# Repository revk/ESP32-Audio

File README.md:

## Amazon

This part if for Amazon - as this is the *manufacturers web site* and so used as proof of title and list price. It is also links to where you can buy.

|ASIN|List price|Title|
|-----|----|----|
|[B0DQH9SK8K](https://www.amazon.co.uk/dp/B0DQH9SK8K)|£35.00|Small ESP32-S3 high quality voice recorder board with stereo TDK ICS 43434 microphones, micro SD card slot, and charger circuit|

## Trademark

This is an open source project, but bear in mind you cannot sell boards bearing the Andrews & Arnold Ltd name, the A&A logo, the registered trademark AJK logo, or the GS1 allocated EANs assigned to Andrews & Arnold Ltd.

# Open†Mic

(† Open source)

This project provides software and PCB designs for working with I2S microphone and speaker, most notably a self contained battery operated audio recorder to micro SD card.

The software provides working for a number of different use cases.

The hardware is an audio recorder, but the [LED](https://github.com/revk/ESP32-LED) project also has audio hardware with microphones and speakers.

## Why use this?

There are loads of microphones and dictaphones at sensible prices, so why use this?

The main reason is flexibility - it is open source - the hardware can do a lot, and it already allows record to SD and upload by web post. It can eventually be a Bluetooth microphone, or a telephone or intercom, etc. You get to do what you like, and can make suggestions and pull requests and load your own code.

The other feature, which is becoming rarer these days, is that it is *stand alone*. No subscription. No accounts or sign up. No cloud services. Nobody training AI on your data.

## Button

Button works with short or long press (long is 3s).

* press to answer or end incoming SIP call
* press to start or stop recording
* hold (1s) to reject incoming SIP call
* hold (1s) to make a call
* hold (3s) to enter power off (will upload files at this point if option selected) - there is also an auto power off feature
* press to power back on

## Microphone

The software is designed to work with I2S audio input, and is coded and tested for two specific microphones. Others may work, but I2S has a number of options - so ask me if you need some other settings.

* [TDK T3902](https://www.lcsc.com/datasheet/lcsc_datasheet_2401291125_TDK-InvenSense-MMICT390200012_C3171752.pdf) is an I2S PDM microphone (so 16 bits per sample)
* [TDK ICS-43434](https://www.lcsc.com/datasheet/lcsc_datasheet_2312010321_TDK-InvenSense-ICS-43434_C5656610.pdf) is an I2S microphone (24 bits) with sample rates up to 51.6kHz

The software can work with one or two microphones (i.e. mono or stereo). When two microphones, they are the same type, on the same bus, with one wired as *left* and one as *right* channel. 

## Speaker

For I2S output the [MAX98357A](https://www.lcsc.com/datasheet/lcsc_datasheet_2106070436_Analog-Devices-Inc--Maxim-Integrated-MAX98357AEWL-T_C2682619.pdf) is recommended. This can be one chip working as *left*, *right*, or *left+right* channels, or as two chips on the same bus, one as *left* and one as *right*.

* `spkrate` sets the speaker rate, which (for the MAX98357A) can be 8kHz, 16kHz, 32kHz, 44.1kHz, 48kHz, 88.2kHz, or 96kHz.

## Input processing

The input from the I2S microphones can be mono or stereo, and can be 16 or 24 bits. If a PDM microphone is used it is always 16 bits. If the ICS-43434 microphone is used it is received as 24 bits which can either be passed on unprocessed, or converted to 16 bits.

* `micws` is the GPIO for the channel, if not set it is assumed to be PDM mode
* `micrate` sets the sample rate
* `micstereo` is set for stereo working
* `micright` is set for *right* channel when mono.
* `micgain` sets the gain for processing 24 bits to 16

When `micgain` is set to `0`, or when using a PDM microphone, the samples (stereo or mono) are used as received, with no processing. This means for PDM mode this is 16 bits per sample, and for ICS-43434 it is 24 bits per sample.

When `micgain` is not `0`, for ICS-43434, the 24 bit samples are processed by multiplying by `micgain/256` and clipping to 16 bits (`-32768` to `32767`). A `micgain` of `8` works well for speech.

## Output

The output via the speaker can be one of the following - normally managed via MQTT control messages or web interface, though SIP is automatic when a call arrives.

* Morse code (including prosigns in `[]`, e.g. `[INT]`) and punctuation
* DTMF
* Playing a WAV file from SD card (TODO)
* SIP (see below)

The format will depend on the source - the MAX98357A can handle 16, 24, or 32 bits per channel.

## Audio recorder

The main use of this software is as an *audio recorder*. This will record from the microphone(s) to a WAV file on the micro SD card. It allows a `button` GPIO to start/stop recording and power on/off. It allows for a separate WS2812 record status LED. The PCB design includes LiPo charging.

Options are planned:-

* Stream audio over WiFI by some means
* Stream audio over bluetooth, if ever I work out how to do that

An option exists to upload files to a web page as a `POST`, renaming the file slightly once uploaded so not uploaded twice. This is done when you hold the button to *power off`*.

An option exists to delete old files if space needed for new file.

## SIP working

The software allows settings `siphost`, `sipuser`, and `sippass`, such that the device registers with a SIP server.

Once registered it can then accept a call, and pass audio both ways over RTP, 8kHz alaw. Only one call at a time.

* The microphone is changed to mono (channel selected by `micright`) 8kHz, and either 16 bit PDM, or processed 24 bit to 16 bit using `micgain`, and then companded to alaw.
* The speaker is sent dual mono audio expanded from 8kHz alaw to 16 bits per sample.

Note that there is no echo cancellation, so a caller is likely to hear their own audio come back to them.

Once the call is complete, the audio processing reverts to previous settings.

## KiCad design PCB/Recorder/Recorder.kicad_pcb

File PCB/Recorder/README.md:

# Audio recorder board

The Audio record board provides a shirt mount Audio board.

Features

* LiPo battery handling and charging
* Mic, stereo TDK ICS 43434 24 bit
* SD card slot
* Button to start/stop recording, etc.

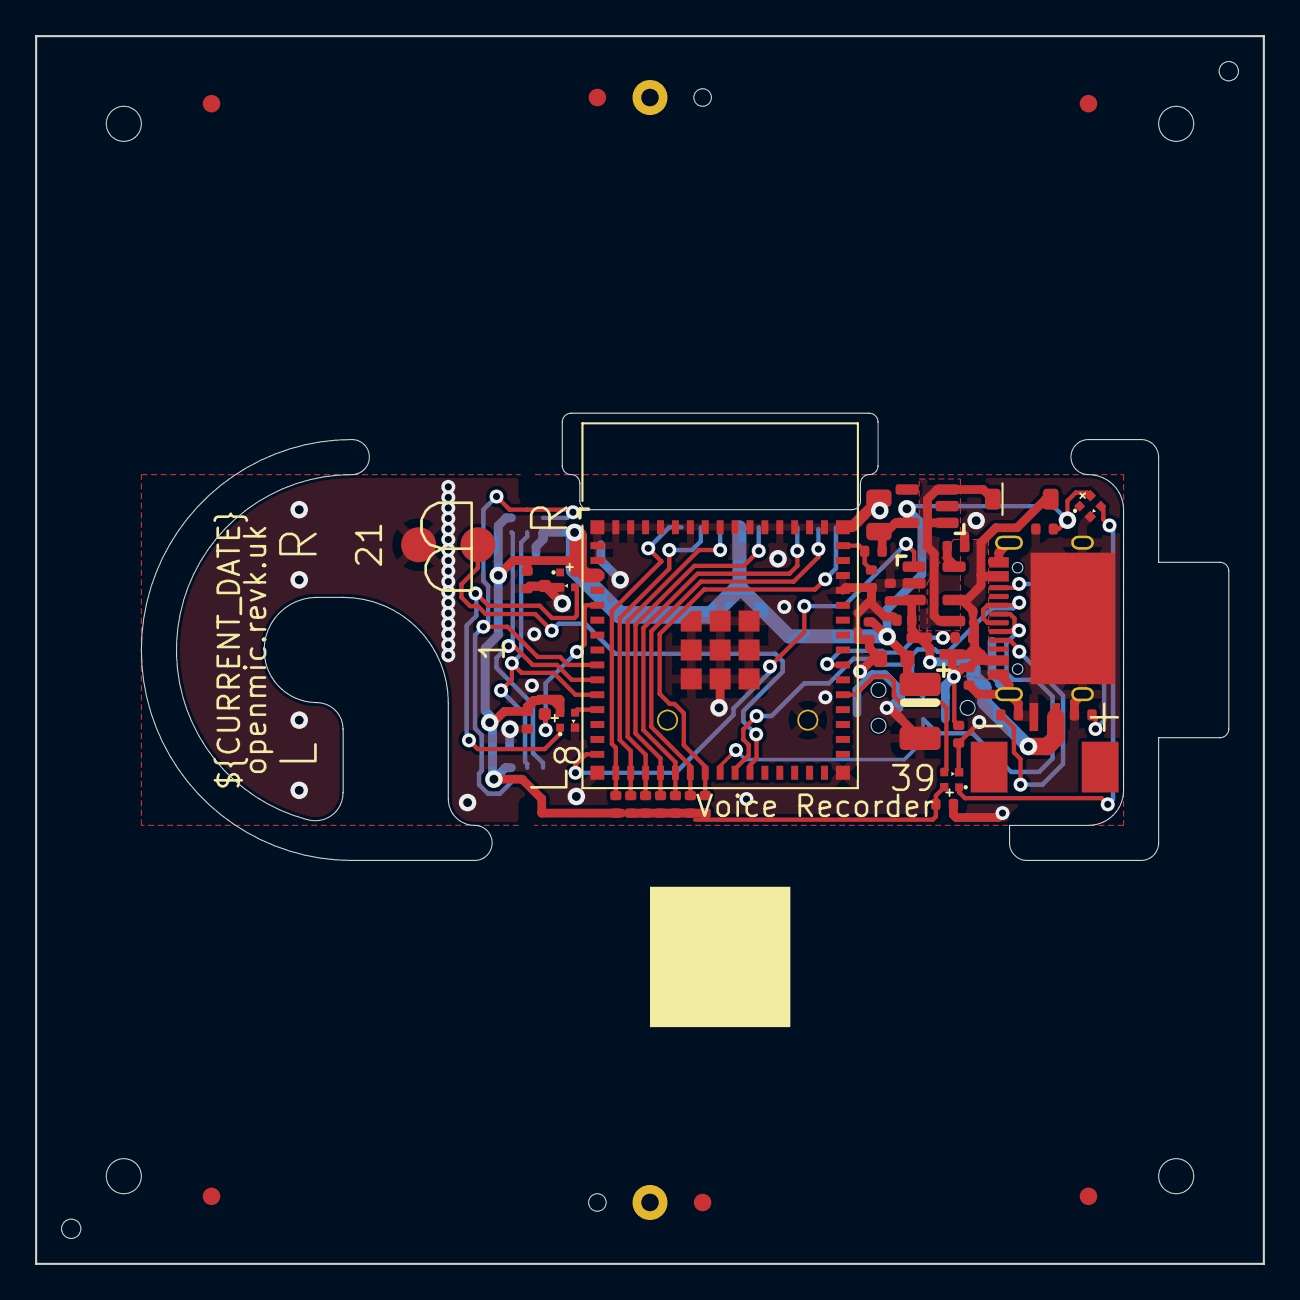
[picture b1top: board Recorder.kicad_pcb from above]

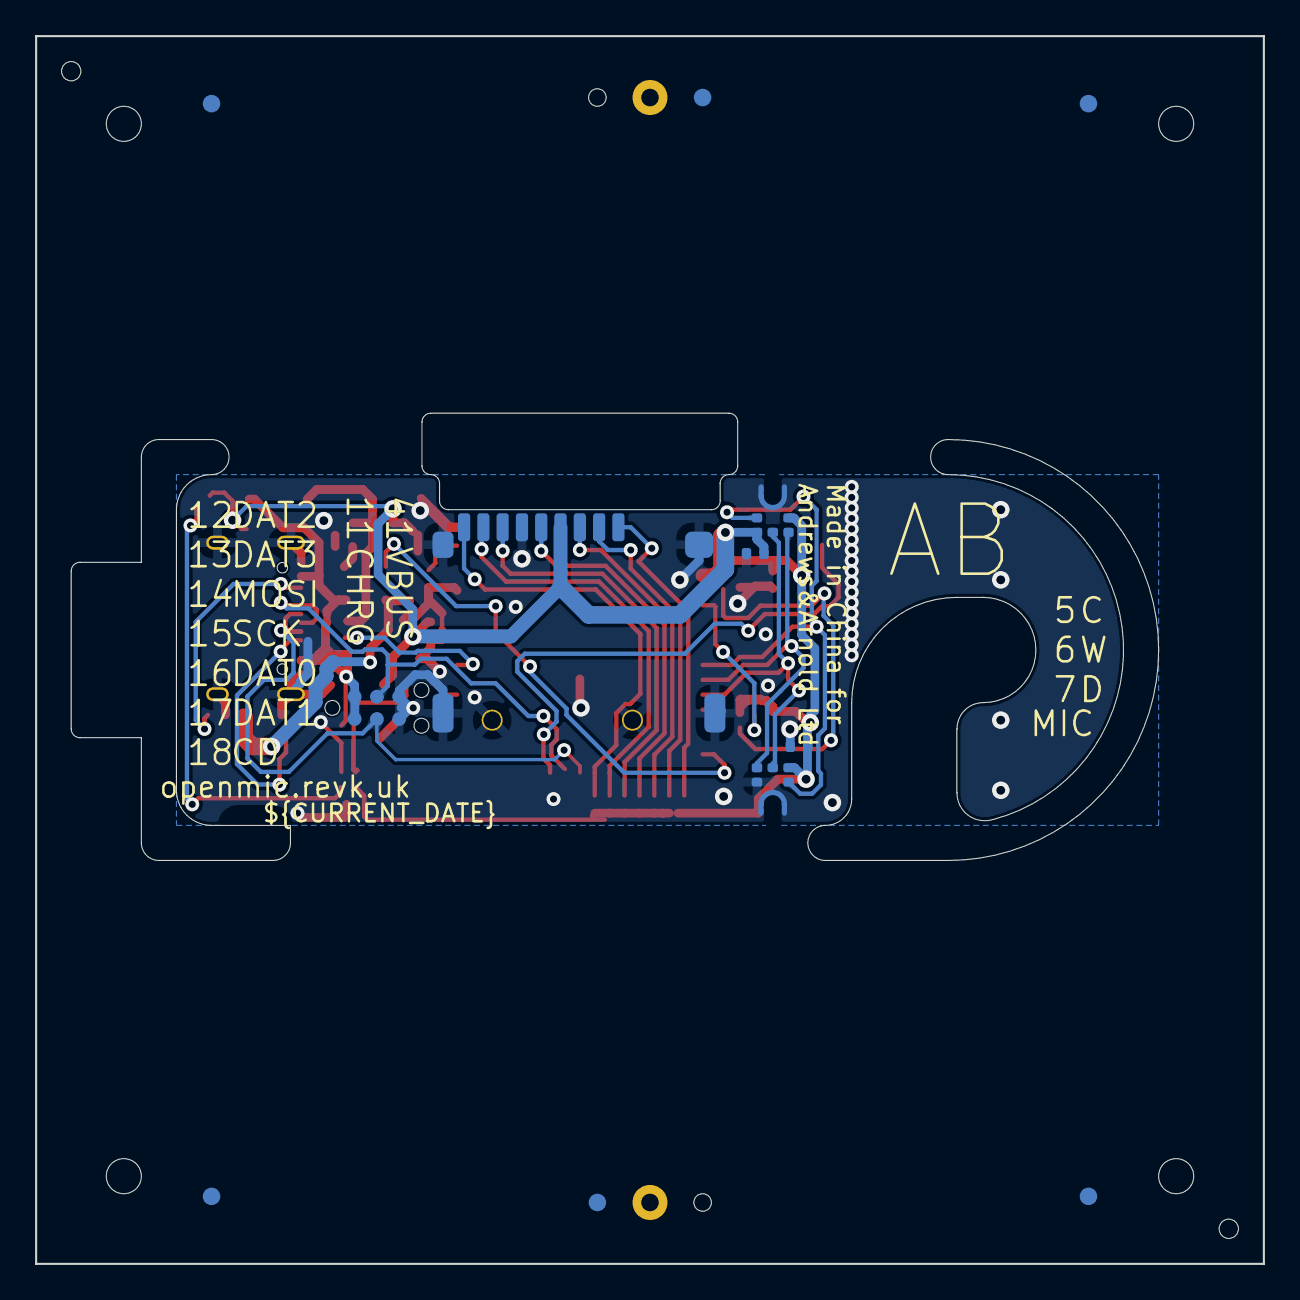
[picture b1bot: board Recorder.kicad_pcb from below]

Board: 2 copper layers, 70.0 x 70.0 mm, 47 parts (7 on the bottom side), 29 nets.

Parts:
C1: 220uF Tant; CP_EIA-3528-21_Kemet-B
C2, C4, C5, C6, C8, C10, C13: 100nF; C_0402
C3: 22uF; C_0603
C7, C11: 10uF 6.3V; C_0402
C9: 1uF; C_0402
C16: 100uF; C_0805
D1, D4, D5, D6: XL-1010RGBC-WS2812B; SMD1010
D2: DFN1006-2L
D3: MBR0530; D_SOD-123
J1: Battery; 1.25T-2PWT (Molex 532610271)
J2: Reset; AA-Pad
J3: TC2030-USB-NL-DS; Tag-Connect_TC2030-IDC-NL_2x03_P1.27mm_Vertical
J4: TF_PUSH
J5: USB-C-Socket-H
PCB1: 70x70; PCB7070
Q2: CJ2301; SOT-23
R1, R2, R3, R7, R8, R9, R10, R11, R12, R13, R14: 10K; R_0402
R5, R6: 5K1; R_0402
SW1: SW_Push; TS-1092S-B3D2-G
U1: R; ICS43434_MEMS_Mic_Open
U2: L; ICS43434_MEMS_Mic_Open
U3: TP4054; SOT-23-5
U4: ME6211C33M5G-N; SOT-23-5
U6: ESP32-S3-MINI-1
V1, V2: VCUT70N

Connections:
+3V3: C1.1, C2.1, C3.1, C4.1, C5.1, C6.1, C8.2, C10.1, C13.2, C16.1, D1.2 (+), D4.2 (+), D5.2 (+), D6.2 (+), J4.4 (VDD), R2.1, R3.1, R9.1, R10.1, R11.1, R12.1, R13.1, R14.1, U1.2 (LR), U1.5 (VDD), U2.5 (VDD), U4.5 (OUT), U6.3 (3V3)
BLINK: D1.4 (I), U6.35 (GPIO39)
BUTTON: SW1.2, U6.5 (GPIO1)
CHARGING: U3.1 (STAT), U6.15 (GPIO11)
D+: J3.4 (D+), J5.A6 (D+), J5.B6 (D+), U6.24 (GPIO20)
D-: J3.3 (D-), J5.A7 (D-), J5.B7 (D-), U6.23 (GPIO19)
GND: C1.2, C2.2, C3.2, C4.2, C5.2, C6.2, C7.2, C8.1, C9.2, C10.2, C11.2, C13.1, C16.2, D1.3 (-), D2.1, D4.3 (-), D5.3 (-), D6.3 (-), J1.2, J2.1, J3.5 (GND), J3.6 (GND), J4.6 (VSS), J4.S (SHIELD), J5.A1 (GND), J5.A12 (GND), J5.B1 (GND), J5.B12 (GND), J5.S1 (SHIELD), R1.1, R5.2, R6.1, R8.2, SW1.1, U1.3 (GND), U2.2 (LR), U2.3 (GND), U3.2 (VSS), U4.2 (GND), U6.1 (GND), U6.2 (GND), U6.42 (GND), U6.43 (GND), U6.46 (GND), U6.47 (GND), U6.48 (GND), U6.49 (GND), U6.50 (GND), U6.51 (GND), U6.52 (GND), U6.53 (GND), U6.54 (GND), U6.55 (GND), U6.56 (GND), U6.57 (GND), U6.58 (GND), U6.59 (GND), U6.60 (GND), U6.61 (GND), U6.62 (GND), U6.63 (GND), U6.64 (GND), U6.65 (GND)
LEDMIC: D5.4 (I), U6.12 (GPIO8)
unnamed: D1.1 (O), D6.4 (I)
unnamed: D3.1 (K), Q2.2 (S), U4.1 (IN), U4.3 (EN)
unnamed: D4.4 (I), D5.1 (O)
unnamed: J2.2, U6.25 (GPIO21)
unnamed: J5.A5 (CC1), R5.1
unnamed: J5.B5 (CC2), R6.2
unnamed: R1.2, U3.5 (PROG)
unnamed: C9.1, R2.2, U6.45 (EN)
unnamed: R7.1, U6.37 (GPIO41)
SCK: U1.4 (SCK), U2.4 (SCK), U6.9 (GPIO5)
SD: U1.6 (SD), U2.6 (SD), U6.11 (GPIO7)
SDCD: J4.9 (CD), R3.2, U6.22 (GPIO18)
SDCLK: J4.5 (CLK), R11.2, U6.19 (GPIO15)
SDCMD: J4.3 (CMD), R12.2, U6.18 (GPIO14)
SDDAT0: J4.7 (DAT0), R10.2, U6.20 (GPIO16)
SDDAT1: J4.8 (DAT1), R9.2, U6.21 (GPIO17)
SDDAT2: J4.1 (DAT2), R14.2, U6.16 (GPIO12)
SDDAT3: J4.2 (DAT3/CD), R13.2, U6.17 (GPIO13)
VBAT: C7.1, D2.2, J1.1, Q2.3 (D), U3.3 (VBAT)
VBUS: C11.1, D3.2 (A), J3.1 (VBUS), J3.2 (VBUS), J5.A4 (VBUS), J5.A9 (VBUS), J5.B4 (VBUS), J5.B9 (VBUS), Q2.1 (G), R7.2, R8.1, U3.4 (VDD)
WS: U1.1 (WS), U2.1 (WS), U6.10 (GPIO6)

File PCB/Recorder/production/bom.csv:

Designator,Footprint,Quantity,Value,LCSC Part #
C1,CP_EIA-3528-21_Kemet-B,1,220uF Tant,C122649
"C10, C13, C2, C4, C5, C6, C8",C_0402,7,100nF,
"C11, C7",C_0402,2,10uF 6.3V,C15525
C16,C_0805,1,100uF,C141660
C3,C_0603,1,22uF,
C9,C_0402,1,1uF,
"D1, D4, D5, D6",SMD1010,4,XL-1010RGBC-WS2812B,C5349953
D2,DFN1006-2L,1,~,C5137770
D3,D_SOD-123,1,MBR0530,
J1,1.25T-2PWT (Molex 532610271),1,Battery,C177225
J4,TF_PUSH,1,TF_PUSH,C393941
J5,USB-C-Socket-H,1,USB-C-Socket-H,C709357
Q2,SOT-23,1,CJ2301,C8547
"R1, R10, R11, R12, R13, R14, R2, R3, R7, R8, R9",R_0402,11,10K,
"R5, R6",R_0402,2,5K1,
SW1,TS-1092S-B3D2-G,1,SW_Push,
U1,ICS43434_MEMS_Mic_Open,1,R,C5656610
U2,ICS43434_MEMS_Mic_Open,1,L,C5656610
U3,SOT-23-5,1,TP4054,C668215
U4,SOT-23-5,1,ME6211C33M5G-N,C82942
U6,ESP32-S3-MINI-1,1,ESP32-S3-MINI-1,C3013941

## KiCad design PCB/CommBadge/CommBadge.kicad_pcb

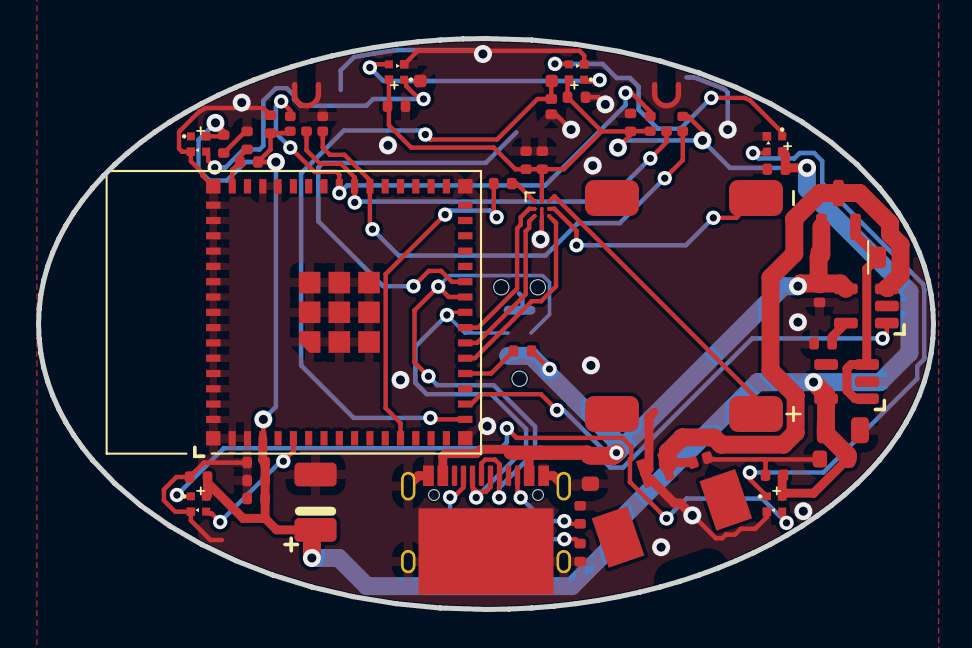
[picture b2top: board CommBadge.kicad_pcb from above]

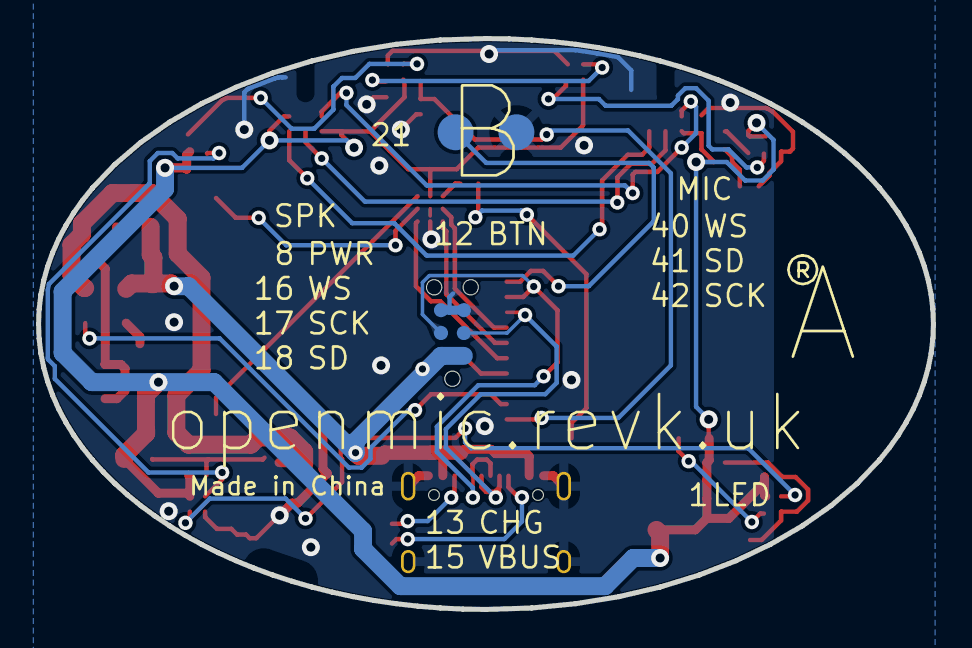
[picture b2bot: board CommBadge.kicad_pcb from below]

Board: 2 copper layers, 49.7 x 31.7 mm, 47 parts (2 on the bottom side), 31 nets.

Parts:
C1: 220uF Tant; CP_EIA-3528-21_Kemet-B
C2, C6, C10, C11, C12, C14, C15, C16, C17, C18: 100nF; C_0402
C3: 22uF; C_0603
C4: 100uF; C_0805
C5: 10uF 35V; C_0603
C7, C8, C13: 10uF; C_0402
C9: 1uF; C_0402
D1, D3: DFN1006-2L
D2: MBR0530; D_SOD-123
D4, D5, D6, D7, D8, D9: XL-1010RGBC-WS2812B; SMD1010
J1: Reset; AA-Pad
J2: Battery; 1.25T-2PWT (Molex 532610271)
J3: TC2030-USB-NL-DS; Tag-Connect_TC2030-IDC-NL_2x03_P1.27mm_Vertical
J5: USB-C-Socket-H
LS1: Speaker; KLJ-Speaker
Q1: CJ2301; SOT-23
R1, R2, R3, R4: 10K; R_0402
R5, R6: 5K1; R_0402
R8: 634K; R_0402
SW2: SW_Push; TS-1092S-B3D2-G
U2: MAX98357A; WLP-1.437mmx1.347mm-0.21mm-ball
U3: TP4054; SOT-23-5
U4: ME6211C33M5G-N; SOT-23-5
U5: L; ICS43434_MEMS_Mic_Open
U6: ESP32-S3-MINI-1
U7: R; ICS43434_MEMS_Mic_Open

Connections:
+3V3: C1.1, C2.1, C3.1, C4.1, C6.2, C7.1, C8.1, C10.2, C11.1, C12.1, C13.1, C14.1, C15.1, C16.1, C17.1, C18.1, D4.2 (+), D5.2 (+), D6.2 (+), D7.2 (+), D8.2 (+), D9.2 (+), R2.1, U2.A2 (VDD), U4.5 (OUT), U5.5 (VDD), U6.3 (3V3), U7.2 (LR), U7.5 (VDD)
CHARGING: U3.1 (STAT), U6.17 (GPIO13)
D+: J3.4 (D+), J5.A6 (D+), J5.B6 (D+), U6.24 (GPIO20)
D-: J3.3 (D-), J5.A7 (D-), J5.B7 (D-), U6.23 (GPIO19)
GND: C1.2, C2.2, C3.2, C4.2, C5.2, C6.1, C7.2, C8.2, C9.2, C10.1, C11.2, C12.2, C13.2, C14.2, C15.2, C16.2, C17.2, C18.2, D1.1, D3.1, D4.3 (-), D5.3 (-), D6.3 (-), D7.3 (-), D8.3 (-), D9.3 (-), J1.1, J2.2, J3.5 (GND), J3.6 (GND), J5.A1 (GND), J5.A12 (GND), J5.B1 (GND), J5.B12 (GND), J5.S1 (SHIELD), R1.1, R3.2, R5.2, R6.1, SW2.1, U2.B2 (GAIN_SLOT), U2.C2 (GND), U3.2 (VSS), U4.2 (GND), U5.2 (LR), U5.3 (GND), U6.1 (GND), U6.2 (GND), U6.42 (GND), U6.43 (GND), U6.46 (GND), U6.47 (GND), U6.48 (GND), U6.49 (GND), U6.50 (GND), U6.51 (GND), U6.52 (GND), U6.53 (GND), U6.54 (GND), U6.55 (GND), U6.56 (GND), U6.57 (GND), U6.58 (GND), U6.59 (GND), U6.60 (GND), U6.61 (GND), U6.62 (GND), U6.63 (GND), U6.64 (GND), U6.65 (GND), U7.3 (GND)
MICSCK: U5.4 (SCK), U6.38 (GPIO42), U7.4 (SCK)
MICSD: U5.6 (SD), U6.37 (GPIO41), U7.6 (SD)
MICWS: U5.1 (WS), U6.36 (GPIO40), U7.1 (WS)
unnamed: D2.1 (K), Q1.2 (S), U4.1 (IN), U4.3 (EN)
unnamed: D4.4 (I), D9.1 (O)
unnamed: D4.1 (O), D5.4 (I)
unnamed: D5.1 (O), D8.4 (I)
unnamed: D6.4 (I), D8.1 (O)
unnamed: D6.1 (O), D7.4 (I)
unnamed: J1.2, U6.25 (GPIO21)
unnamed: J5.A5 (CC1), R5.1
unnamed: J5.B5 (CC2), R6.2
unnamed: LS1.2, U2.B3 (OUTN)
unnamed: LS1.1, U2.A3 (OUTP)
unnamed: R8.1, U2.A1 (~SD_MODE)
unnamed: R1.2, U3.5 (PROG)
unnamed: C9.1, R2.2, U6.45 (EN)
unnamed: R4.2, U6.19 (GPIO15)
PUSH: D3.2, SW2.2, U6.16 (GPIO12)
RGB: D9.4 (I), U6.5 (GPIO1)
SKPPWR: R8.2, U6.12 (GPIO8)
SKPSCK: U2.C1 (BCLK), U6.21 (GPIO17)
SKPSD: U2.B1 (DIN), U6.22 (GPIO18)
SKPWS: U2.C3 (LRCLK), U6.20 (GPIO16)
VBAT: D1.2, J2.1, Q1.3 (D), U3.3 (VBAT)
VBUS: C5.1, D2.2 (A), J3.1 (VBUS), J3.2 (VBUS), J5.A4 (VBUS), J5.A9 (VBUS), J5.B4 (VBUS), J5.B9 (VBUS), Q1.1 (G), R3.1, R4.1, U3.4 (VDD)

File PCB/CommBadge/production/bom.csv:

Designator,Footprint,Quantity,Value,LCSC Part #
C1,CP_EIA-3528-21_Kemet-B,1,220uF Tant,C122649
"C10, C11, C12, C14, C15, C16, C17, C18, C2, C6",C_0402,10,100nF,
"C13, C7, C8",C_0402,3,10uF,C15525
C3,C_0603,1,22uF,
C4,C_0805,1,100uF,C141660
C5,C_0603,1,10uF 35V,C194427
C9,C_0402,1,1uF,
"D1, D3",DFN1006-2L,2,~,C5137770
D2,D_SOD-123,1,MBR0530,
"D4, D5, D6, D7, D8, D9",SMD1010,6,XL-1010RGBC-WS2812B,C5349953
J2,1.25T-2PWT (Molex 532610271),1,Battery,C177225
J5,USB-C-Socket-H,1,USB-C-Socket-H,C709357
LS1,KLJ-Speaker,1,Speaker,C18186315
Q1,SOT-23,1,CJ2301,C5224170
"R1, R2, R3, R4",R_0402,4,10K,
"R5, R6",R_0402,2,5K1,
R8,R_0402,1,634K,
SW2,TS-1092S-B3D2-G,1,SW_Push,
U2,WLP-1.437mmx1.347mm-0.21mm-ball,1,MAX98357A,
U3,SOT-23-5,1,TP4054,C668215
U4,SOT-23-5,1,ME6211C33M5G-N,C82942
U5,ICS43434_MEMS_Mic_Open,1,L,C5656610
U6,ESP32-S3-MINI-1,1,ESP32-S3-MINI-1,C3013941
U7,ICS43434_MEMS_Mic_Open,1,R,C5656610

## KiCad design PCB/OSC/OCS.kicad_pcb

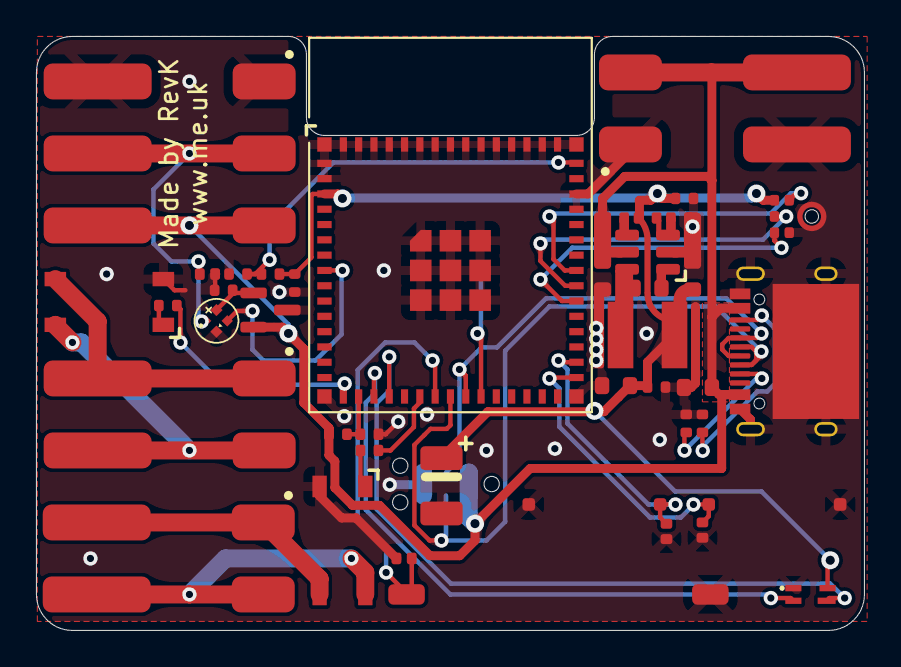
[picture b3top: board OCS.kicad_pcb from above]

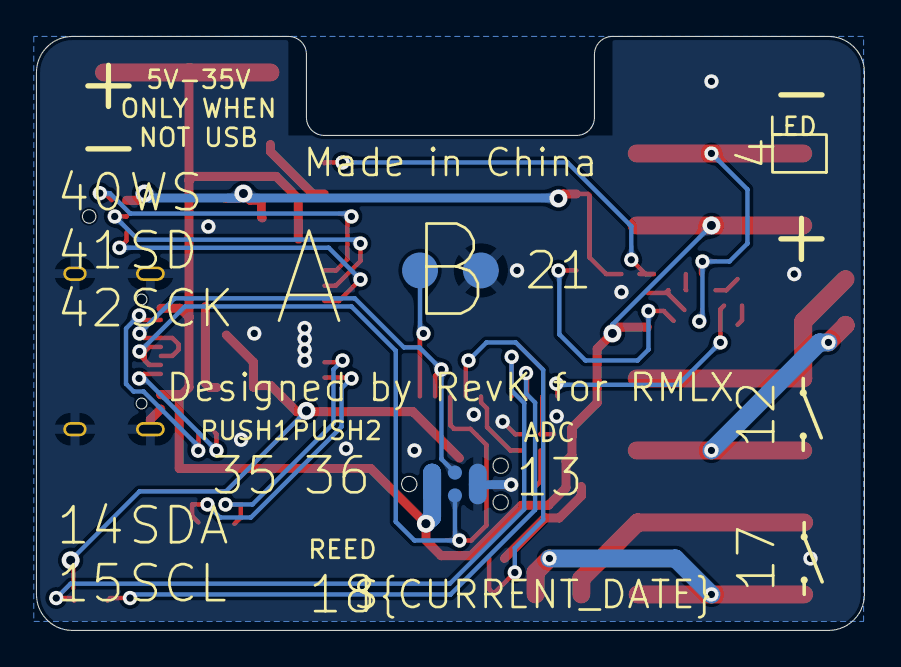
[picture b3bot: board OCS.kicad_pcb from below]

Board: 2 copper layers, 46.0 x 33.0 mm, 44 parts (2 on the bottom side), 29 nets.

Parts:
C1: 220uF Tant; CP_EIA-3528-21_Kemet-B
C2, C15: 100nF; C_0402
C3: 22uF; C_0603
C5: 10uF 35V; C_0603
C7, C8: 10uF; C_0402
C9: 1uF; C_0402
C10: 10uF 35V; C_0603_
C11: 10uF 6.3V; C_0603_
C12: 100nF; C_0603_
D1: XL-1010RGBC-WS2812B; SMD1010
D2, D3, D4, D5: DFN1006-2L
J1: Reset; AA-Pad
J2: Wago; WAGO-2060-453-998-404
J3: TC2030-USB-NL-DS; Tag-Connect_TC2030-IDC-NL_2x03_P1.27mm_Vertical
J4: DC; WAGO-2060-452-998-404
J5: USB-C-Socket-H
J6: RELAY1; WAGO-2060-452-998-404
J7: RELAY2; WAGO-2060-452-998-404
L2: 10uH; L_4x4_
R1: 124K; R_0402
R2, R3: 10K; R_0402
R4: 124k; R_0402_
R5, R6: 5K1; R_0402
R7, R10: 1K; R_0402
R14: 39k2; R_0402_
R15: 1M; R_0402_
SW1, SW3: SW_Push; TS-1092S-B3D2-G
SW2: SW_Reed; Reed-59170
U1: ICS43434_MEMS_Mic
U3, U8: Relay; SO-4_4.4x4.3mm_P2.54mm
U4: 78L05; SOT-23
U6: ESP32-S3-MINI-1
U7: MD8942; SOT-23-6-MD8942
U9: VEML6040

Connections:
+3V3: C1.1, C2.1, C3.1, C7.1, C8.1, R2.1, U1.5 (VDD), U6.3 (3V3), U7.8 (VOUT), U9.4 (VDD)
ADC: R1.2, R3.1, U6.17 (GPIO13)
D+: J3.4 (D+), J5.A6 (D+), J5.B6 (D+), U6.24 (GPIO20)
D-: J3.3 (D-), J5.A7 (D-), J5.B7 (D-), U6.23 (GPIO19)
DC: C5.1, J2.3, J3.1 (VBUS), J3.2 (VBUS), J4.2, J5.A4 (VBUS), J5.A9 (VBUS), J5.B4 (VBUS), J5.B9 (VBUS), R1.1, U4.2 (IN), U7.5 (VIN)
GND: C1.2, C2.2, C3.2, C5.2, C7.2, C8.2, C9.2, C15.2, D1.3 (-), D2.1, D3.1, D4.1, D5.1, J1.1, J2.1, J3.5 (GND), J3.6 (GND), J4.1, J5.A1 (GND), J5.A12 (GND), J5.B1 (GND), J5.B12 (GND), J5.S1 (SHIELD), R3.2, R5.2, R6.1, SW1.1, SW2.2, SW3.1, U1.2 (LR), U1.3 (GND), U3.2, U4.3 (GND), U6.1 (GND), U6.2 (GND), U6.42 (GND), U6.43 (GND), U6.46 (GND), U6.47 (GND), U6.48 (GND), U6.49 (GND), U6.50 (GND), U6.51 (GND), U6.52 (GND), U6.53 (GND), U6.54 (GND), U6.55 (GND), U6.56 (GND), U6.57 (GND), U6.58 (GND), U6.59 (GND), U6.60 (GND), U6.61 (GND), U6.62 (GND), U6.63 (GND), U6.64 (GND), U6.65 (GND), U7.2 (GND), U7.7 (GND), U8.2, U9.1 (GND)
LED1: D1.4 (I), U6.8 (GPIO4)
LED2: D1.1 (O), D2.2, J2.2
MICSCK: U1.4 (SCK), U6.38 (GPIO42)
MICSD: U1.6 (SD), U6.37 (GPIO41)
MICWS: U1.1 (WS), U6.36 (GPIO40)
unnamed: C15.1, D1.2 (+), U4.1 (OUT)
unnamed: J1.2, U6.25 (GPIO21)
unnamed: J5.A5 (CC1), R5.1
unnamed: J5.B5 (CC2), R6.2
unnamed: J6.1, U3.3
unnamed: J6.2, U3.4
unnamed: J7.1, U8.3
unnamed: J7.2, U8.4
unnamed: R7.1, U3.1
unnamed: R10.1, U8.1
unnamed: C9.1, R2.2, U6.45 (EN)
PUSH1: D3.2, SW3.2, U6.31 (GPIO35)
PUSH2: D4.2, SW1.2, U6.32 (GPIO36)
REED: D5.2, SW2.1, U6.22 (GPIO18)
RELAY1: R7.2, U6.16 (GPIO12)
RELAY2: R10.2, U6.21 (GPIO17)
SCL: U6.19 (GPIO15), U9.3 (SCL)
SDA: U6.18 (GPIO14), U9.2 (SDA)

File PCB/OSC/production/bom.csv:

Designator,Footprint,Quantity,Value,LCSC Part #
C1,CP_EIA-3528-21_Kemet-B,1,220uF Tant,C122649
C10,C_0603_,1,10uF 35V,C194427
C11,C_0603_,1,10uF 6.3V,C1691
C12,C_0603_,1,100nF,
"C15, C2",C_0402,2,100nF,
C3,C_0603,1,22uF,
C5,C_0603,1,10uF 35V,C194427
"C7, C8",C_0402,2,10uF,C15525
C9,C_0402,1,1uF,
D1,SMD1010,1,XL-1010RGBC-WS2812B,C5349953
"D2, D3, D4, D5",DFN1006-2L,4,~,C5137770
J2,WAGO-2060-453-998-404,1,Wago,C2765056
J4,WAGO-2060-452-998-404,1,DC,C2765055
J5,USB-C-Socket-H,1,USB-C-Socket-H,C709357
J6,WAGO-2060-452-998-404,1,RELAY1,C2765055
J7,WAGO-2060-452-998-404,1,RELAY2,C2765055
L2,L_4x4_,1,10uH,
R1,R_0402,1,124K,
"R10, R7",R_0402,2,1K,
R14,R_0402_,1,39k2,
R15,R_0402_,1,1M,
"R2, R3",R_0402,2,10K,
R4,R_0402_,1,124k,
"R5, R6",R_0402,2,5K1,
"SW1, SW3",TS-1092S-B3D2-G,2,SW_Push,
SW2,Reed-59170,1,SW_Reed,C315909
U1,ICS43434_MEMS_Mic,1,ICS43434_MEMS_Mic,C5656610
"U3, U8",SO-4_4.4x4.3mm_P2.54mm,2,Relay,C2691608
U4,SOT-23,1,78L05,C22392284
U6,ESP32-S3-MINI-1,1,ESP32-S3-MINI-1,C3013941
U7,SOT-23-6-MD8942,1,MD8942,C2684786
U9,VEML6040,1,VEML6040,C78465

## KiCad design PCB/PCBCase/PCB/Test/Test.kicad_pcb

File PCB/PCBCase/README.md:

# PCB Case

This is designed to take an KICad 7 `.kicad_pcb` file and produce an openscad file that is the case. See `--help` for arguments.

[Models](models/README.md)

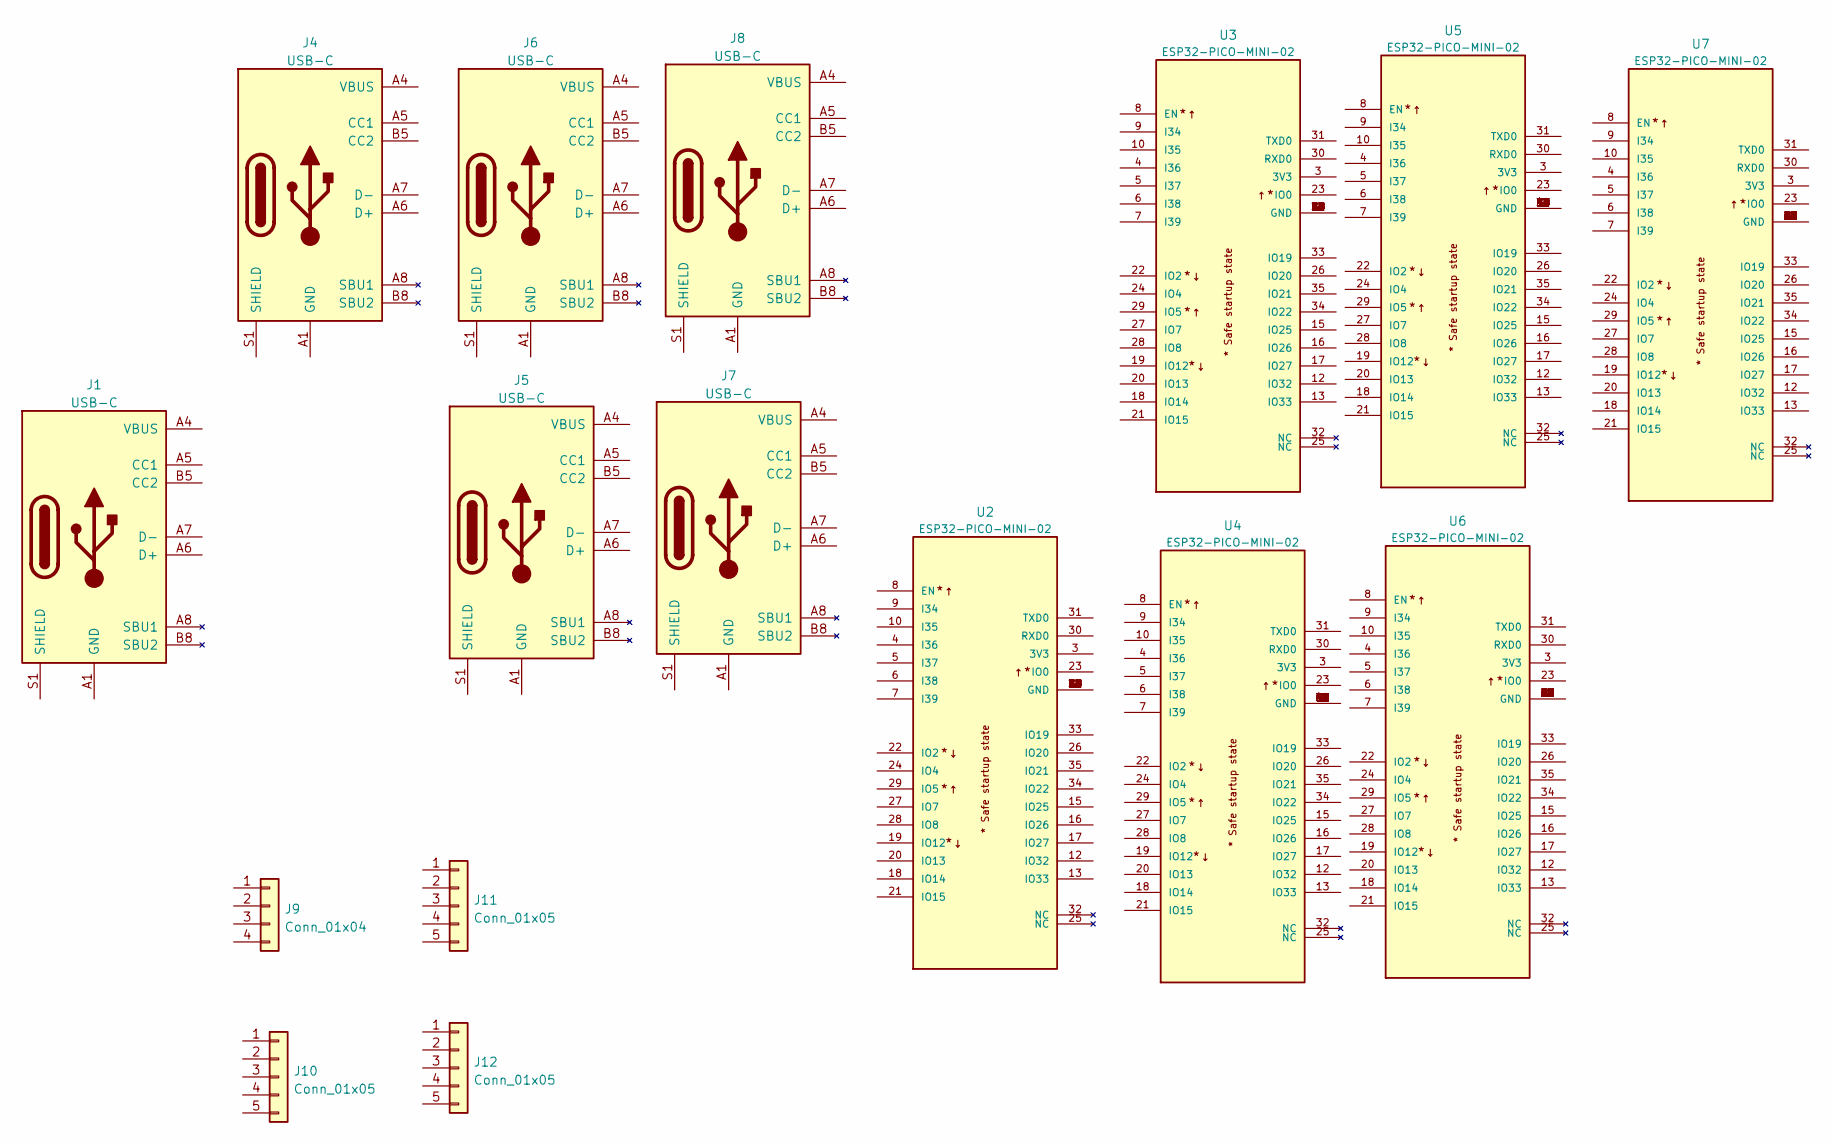
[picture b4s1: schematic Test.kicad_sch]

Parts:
J1, J4, J5, J6, J7, J8: USB-C; USC16-TR-Round
J9: Conn_01x04; JLC-PinHeader_1x04_P2.54mm_Right
J10: Conn_01x05; PTSM-HH-5-RA-P
J11: Conn_01x05; PTSM-HH-5-RA
J12: Conn_01x05; PTSM-HH-5-RA-P-SMD
U2, U3, U4, U5, U6, U7: ESP32-PICO-MINI-02; PARTREV v1.0

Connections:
unnamed: J1.A1 (GND), J1.A12 (GND), J1.B1 (GND), J1.B12 (GND)
unnamed: J1.A4 (VBUS), J1.A9 (VBUS), J1.B4 (VBUS), J1.B9 (VBUS)
unnamed: J1.A6 (D+), J1.B6 (D+)
unnamed: J1.A7 (D-), J1.B7 (D-)
unnamed: J4.A1 (GND), J4.A12 (GND), J4.B1 (GND), J4.B12 (GND)
unnamed: J4.A4 (VBUS), J4.A9 (VBUS), J4.B4 (VBUS), J4.B9 (VBUS)
unnamed: J4.A6 (D+), J4.B6 (D+)
unnamed: J4.A7 (D-), J4.B7 (D-)
unnamed: J5.A1 (GND), J5.A12 (GND), J5.B1 (GND), J5.B12 (GND)
unnamed: J5.A4 (VBUS), J5.A9 (VBUS), J5.B4 (VBUS), J5.B9 (VBUS)
unnamed: J5.A6 (D+), J5.B6 (D+)
unnamed: J5.A7 (D-), J5.B7 (D-)
unnamed: J6.A1 (GND), J6.A12 (GND), J6.B1 (GND), J6.B12 (GND)
unnamed: J6.A4 (VBUS), J6.A9 (VBUS), J6.B4 (VBUS), J6.B9 (VBUS)
unnamed: J6.A6 (D+), J6.B6 (D+)
unnamed: J6.A7 (D-), J6.B7 (D-)
unnamed: J7.A1 (GND), J7.A12 (GND), J7.B1 (GND), J7.B12 (GND)
unnamed: J7.A4 (VBUS), J7.A9 (VBUS), J7.B4 (VBUS), J7.B9 (VBUS)
unnamed: J7.A6 (D+), J7.B6 (D+)
unnamed: J7.A7 (D-), J7.B7 (D-)
unnamed: J8.A1 (GND), J8.A12 (GND), J8.B1 (GND), J8.B12 (GND)
unnamed: J8.A4 (VBUS), J8.A9 (VBUS), J8.B4 (VBUS), J8.B9 (VBUS)
unnamed: J8.A6 (D+), J8.B6 (D+)
unnamed: J8.A7 (D-), J8.B7 (D-)
unnamed: U2.1 (GND), U2.2 (GND), U2.11 (GND), U2.14 (GND), U2.36 (GND), U2.37 (GND), U2.38 (GND), U2.39 (GND), U2.40 (GND), U2.41 (GND), U2.42 (GND), U2.43 (GND), U2.44 (GND), U2.45 (GND), U2.46 (GND), U2.47 (GND), U2.48 (GND), U2.49 (GND), U2.50 (GND), U2.51 (GND), U2.52 (GND), U2.53 (GND)
unnamed: U3.1 (GND), U3.2 (GND), U3.11 (GND), U3.14 (GND), U3.36 (GND), U3.37 (GND), U3.38 (GND), U3.39 (GND), U3.40 (GND), U3.41 (GND), U3.42 (GND), U3.43 (GND), U3.44 (GND), U3.45 (GND), U3.46 (GND), U3.47 (GND), U3.48 (GND), U3.49 (GND), U3.50 (GND), U3.51 (GND), U3.52 (GND), U3.53 (GND)
unnamed: U4.1 (GND), U4.2 (GND), U4.11 (GND), U4.14 (GND), U4.36 (GND), U4.37 (GND), U4.38 (GND), U4.39 (GND), U4.40 (GND), U4.41 (GND), U4.42 (GND), U4.43 (GND), U4.44 (GND), U4.45 (GND), U4.46 (GND), U4.47 (GND), U4.48 (GND), U4.49 (GND), U4.50 (GND), U4.51 (GND), U4.52 (GND), U4.53 (GND)
unnamed: U5.1 (GND), U5.2 (GND), U5.11 (GND), U5.14 (GND), U5.36 (GND), U5.37 (GND), U5.38 (GND), U5.39 (GND), U5.40 (GND), U5.41 (GND), U5.42 (GND), U5.43 (GND), U5.44 (GND), U5.45 (GND), U5.46 (GND), U5.47 (GND), U5.48 (GND), U5.49 (GND), U5.50 (GND), U5.51 (GND), U5.52 (GND), U5.53 (GND)
unnamed: U6.1 (GND), U6.2 (GND), U6.11 (GND), U6.14 (GND), U6.36 (GND), U6.37 (GND), U6.38 (GND), U6.39 (GND), U6.40 (GND), U6.41 (GND), U6.42 (GND), U6.43 (GND), U6.44 (GND), U6.45 (GND), U6.46 (GND), U6.47 (GND), U6.48 (GND), U6.49 (GND), U6.50 (GND), U6.51 (GND), U6.52 (GND), U6.53 (GND)
unnamed: U7.1 (GND), U7.2 (GND), U7.11 (GND), U7.14 (GND), U7.36 (GND), U7.37 (GND), U7.38 (GND), U7.39 (GND), U7.40 (GND), U7.41 (GND), U7.42 (GND), U7.43 (GND), U7.44 (GND), U7.45 (GND), U7.46 (GND), U7.47 (GND), U7.48 (GND), U7.49 (GND), U7.50 (GND), U7.51 (GND), U7.52 (GND), U7.53 (GND)

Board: 2 copper layers, 16 parts (6 on the bottom side), 30 nets, no tracks yet.

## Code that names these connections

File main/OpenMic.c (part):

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sd_task (void *arg)
{
   esp_err_t e = 0;
   revk_gpio_input (sdcd);
   sdmmc_slot_config_t slot = SDMMC_SLOT_CONFIG_DEFAULT ();
   slot.clk = sdclk.num;
   slot.cmd = sdcmd.num;
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            jo_string (j, "action", cardstatus = revk_shutting_down (NULL) ? "Card dismounted for shutdown" : "Remove card");
            revk_info ("SD", &j);
            b.dodismount = 0;
            while ((b.sdpresent = revk_gpio_get (sdcd)))
               sleep (1);
            continue;
         }
         if (!(b.sdpresent = revk_gpio_get (sdcd)))
         {                      // No card
            jo_t j = jo_object_alloc ();
            jo_string (j, "error", cardstatus = "Card not present");
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               revk_enable_ap ();
               revk_enable_settings ();
            }
            while (!(b.sdpresent = revk_gpio_get (sdcd)))
               sleep (1);
         }
         if (wifilock)
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         while (!b.doformat && !b.dodismount)
         {
            sdrgb = (sdfile ? 'G' : 'Y');
            if (!(b.sdpresent = revk_gpio_get (sdcd)))
            {                   // card removed
               b.dodismount = 1;
               break;
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         }
      }
   }
   revk_gpio_set (sddat3, 1);
   rtc_gpio_set_direction_in_sleep (sddat3.num, RTC_GPIO_MODE_OUTPUT_ONLY);
   rtc_gpio_set_level (sddat3.num, 1 - sddat3.invert);
   vTaskDelete (NULL);
}

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      }
   }
   rtc_gpio_set_direction_in_sleep (spkpwr.num, RTC_GPIO_MODE_OUTPUT_ONLY);
   rtc_gpio_set_level (spkpwr.num, sddat3.invert);
   vTaskDelete (NULL);
}

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      sip_register (siphost, sipuser, sippass, sip_callback, sipdebug ? sip_debug : NULL);
   // Buttons and LEDs
   revk_gpio_input (button);
   revk_gpio_input (charging);  // On, off, or flashing
   revk_gpio_input (vbus);      // USB status
   uint8_t press = 255;
   uint8_t charge = 0;
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      if (revk_shutting_down (NULL) && b.micon)
         b.micon = 0;
      if (charging.set)
         charge = (charge << 1) | revk_gpio_get (charging);
      if (revk_gpio_get (button))
      {                         // Pressed
         if (press < 255)
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
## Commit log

2024-11-08 Modules
2024-11-08 Concept
2024-11-08 Closer
2024-11-09 Rework concept
2024-11-09 Initial tracking
2024-11-09 Position
2024-11-09 Tidy tracks
2024-11-10 Tidy
2024-11-10 Not LED
2024-11-10 Slot fix
2024-11-11 Cap clash moved
2024-11-14 Annoying noise
2024-11-16 DNP J1 as clashes
2024-11-18 Test
2024-11-18 Pause
2024-11-18 Morse
2024-11-19 SIN table, and various other tweaks
2024-11-19 alaw table
2024-11-20 SIP library
2024-11-20 DTMF
2024-11-20 Comments
2024-11-21 Timing error
2024-11-22 STarted work
2024-11-22 Working on itr
2024-11-22 Working on it
2024-11-22 Config options finally
2024-11-23 SD mount
2024-11-23 Library update
2024-11-23 Main needed more stack
2024-11-23 FFS slow SD no solution yet, may be hardware
2024-11-23 Rework, and pull ups
2024-11-23 Placement
2024-11-24 Resistors
2024-11-24 Still not fast on SD cardm arg
2024-11-24 Writing audio
2024-11-24 Filename
2024-11-24 Naught macro
2024-11-24 Allow no gain 24 bit coding
2024-11-24 Charging LED
2024-11-24 Clipping
2024-11-24 Release code
2024-11-24 release
2024-11-25 Manual
2024-11-25 Typo
2024-11-25 Some progress
2024-11-25 Work on samples and SIP mode
2024-11-25 Fixed some bugs
2024-11-25 Reworked
2024-11-25 Started on OSC board
2024-11-25 Moved
2024-11-25 Getting basic BOM
2024-11-25 Tracked
2024-11-25 No charger?
2024-11-26 Spkpwr shutdown
2024-11-26 Time limit files
2024-11-26 Time
2024-11-26 Initial press ignored
2024-11-26 D'Oh
2024-11-26 Tweak
2024-11-27 New layout
2024-11-27 Correct SS
2024-11-27 Ready to order
2024-11-28 Moved LEDs
2024-11-29 Reworked to have speaker, and VBUS test.
2024-11-29 Call progress
2024-11-29 Testing
2024-11-29 Progress
2024-11-30 Revised tone and DTMF logic
2024-11-30 OK audio linked up
2024-11-30 Ring tone
2024-11-30 More logic
2024-12-01 component
2024-12-01 sip_debug
2024-12-01 Various features
2024-12-01 Cleaner sync beep
2024-12-01 Start on intercom
2024-12-01 Fix oldest file logic
2024-12-01 Upload and delete logic fix
2024-12-01 Tidy SS
2024-12-01 Images
2024-12-01 Info
2024-12-02 STart logci
2024-12-02 Green LED
2024-12-02 wifirecord
2024-12-02 lower power when recording
2024-12-02 Started on HA
2024-12-02 More HA
2024-12-02 HA record button
2024-12-02 More info
2024-12-03 Fix component size
2024-12-03 Renmamed
2024-12-03 Release files under new name
2024-12-03 Prosign and punctuation in Morse
2024-12-03 Button stuff
2024-12-03 Fix footprints
2024-12-03 Tidy up calls
2024-12-04 Tidy wording
2024-12-04 Tidy defaults
2024-12-04 Shorter
2024-12-05 Web Morse/DTMF
2024-12-05 du and ud to allow SMS to morse
2024-12-06 Morse 600Hz is more standard
2024-12-06 Components
2024-12-10 Started IR but not working on test board
2024-12-10 OK hardware works so why not IR s/w
2024-12-10 OK working to get IR raw data now
2024-12-12 No GPIO
2024-12-12 Order
2024-12-12 Mdae longer
2024-12-12 LED tidy
2024-12-12 betarelease
2024-12-13 VBUS
2024-12-14 Auto off mode, and check wifi before upload
2024-12-14 Hook
2024-12-14 Record stats and overrun logic
2024-12-15 Sync file steps
2024-12-15 logging
2024-12-16 upload when no sd card, duh
2024-12-16 Ehit
2024-12-16 LEDs
2024-12-16 library
2024-12-16 Updsate
2024-12-16 File sync and truncation issues fixed
2024-12-16 Allow all data on SD card maybe
2024-12-17 Working on alt to SPI SD mode
2024-12-17 MMC mode (faster than SPI)
2024-12-17 Log read speed
2024-12-17 Formatting works, yay!
2024-12-17 Clean up
2024-12-17 New mic artwork
2024-12-17 Wifi record fix
2024-12-17 Wording
2024-12-17 Dark record
2024-12-17 orange
2024-12-18 Charging is 11 not 18 FFS
2024-12-18 No SPI mode
2024-12-18 New LED logic
2024-12-18 New LED
2024-12-18 No delay uploading now
2024-12-18 charge
2024-12-20 Snap off
2024-12-20 More SS

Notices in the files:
main/OpenMic.c:
Copyright ©2024 Adrian Kennard, Andrews & Arnold Ltd.See LICENCE file for details .GPL 3.0
